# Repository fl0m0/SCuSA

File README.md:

# SCuSA
 **S**cope **Cu**rrent **S**ense **A**mplifier, work in progress

# Design goals

The main reason I designed this current sense amplifier was the need to verify power supplys on PCBs:

* Turn on behavior
* Inrush current
* Short circuit current
* Ripple current

My main requirements were:

* High side measurement > 60 V
* Common mode input range down to 0 V
* Burden voltage below 150 mV
* No galvanic isolation
* Current range up to approx ~3 A
* Accuracy better than 2%
* Bandwith > 150 kHz
* Bonus: Measurement of negative current (for battery charging applications)

I had already built a simple current sense amplifier based on the [INA169](https://www.ti.com/product/INA169) on a breadboard. It fullfilled most of my requirements except the common mode voltage range: 2.7 V made it impossible to measure 1.8 V or 1.0 V voltage supplies which are quite common these days.

I ended up with a design way to complicated and expensive :-) But I really wanted to try out a few interesting ICs:

* [LM27762](https://www.ti.com/product/LM27762): "Low-Noise Positive and Negative Output Integrated Charge Pump Plus LDO"
* [AD8210A](https://www.analog.com/en/products/ad8210.html) or [AD8418A](https://www.analog.com/en/products/ad8418a.html): Very fancy looking "High Voltage, Bidirectional Current Shunt Monitors"

# Current status

* RevA built and partially tested
* Documentation not finished
* RevB work in progress (fixed errors, improvements)

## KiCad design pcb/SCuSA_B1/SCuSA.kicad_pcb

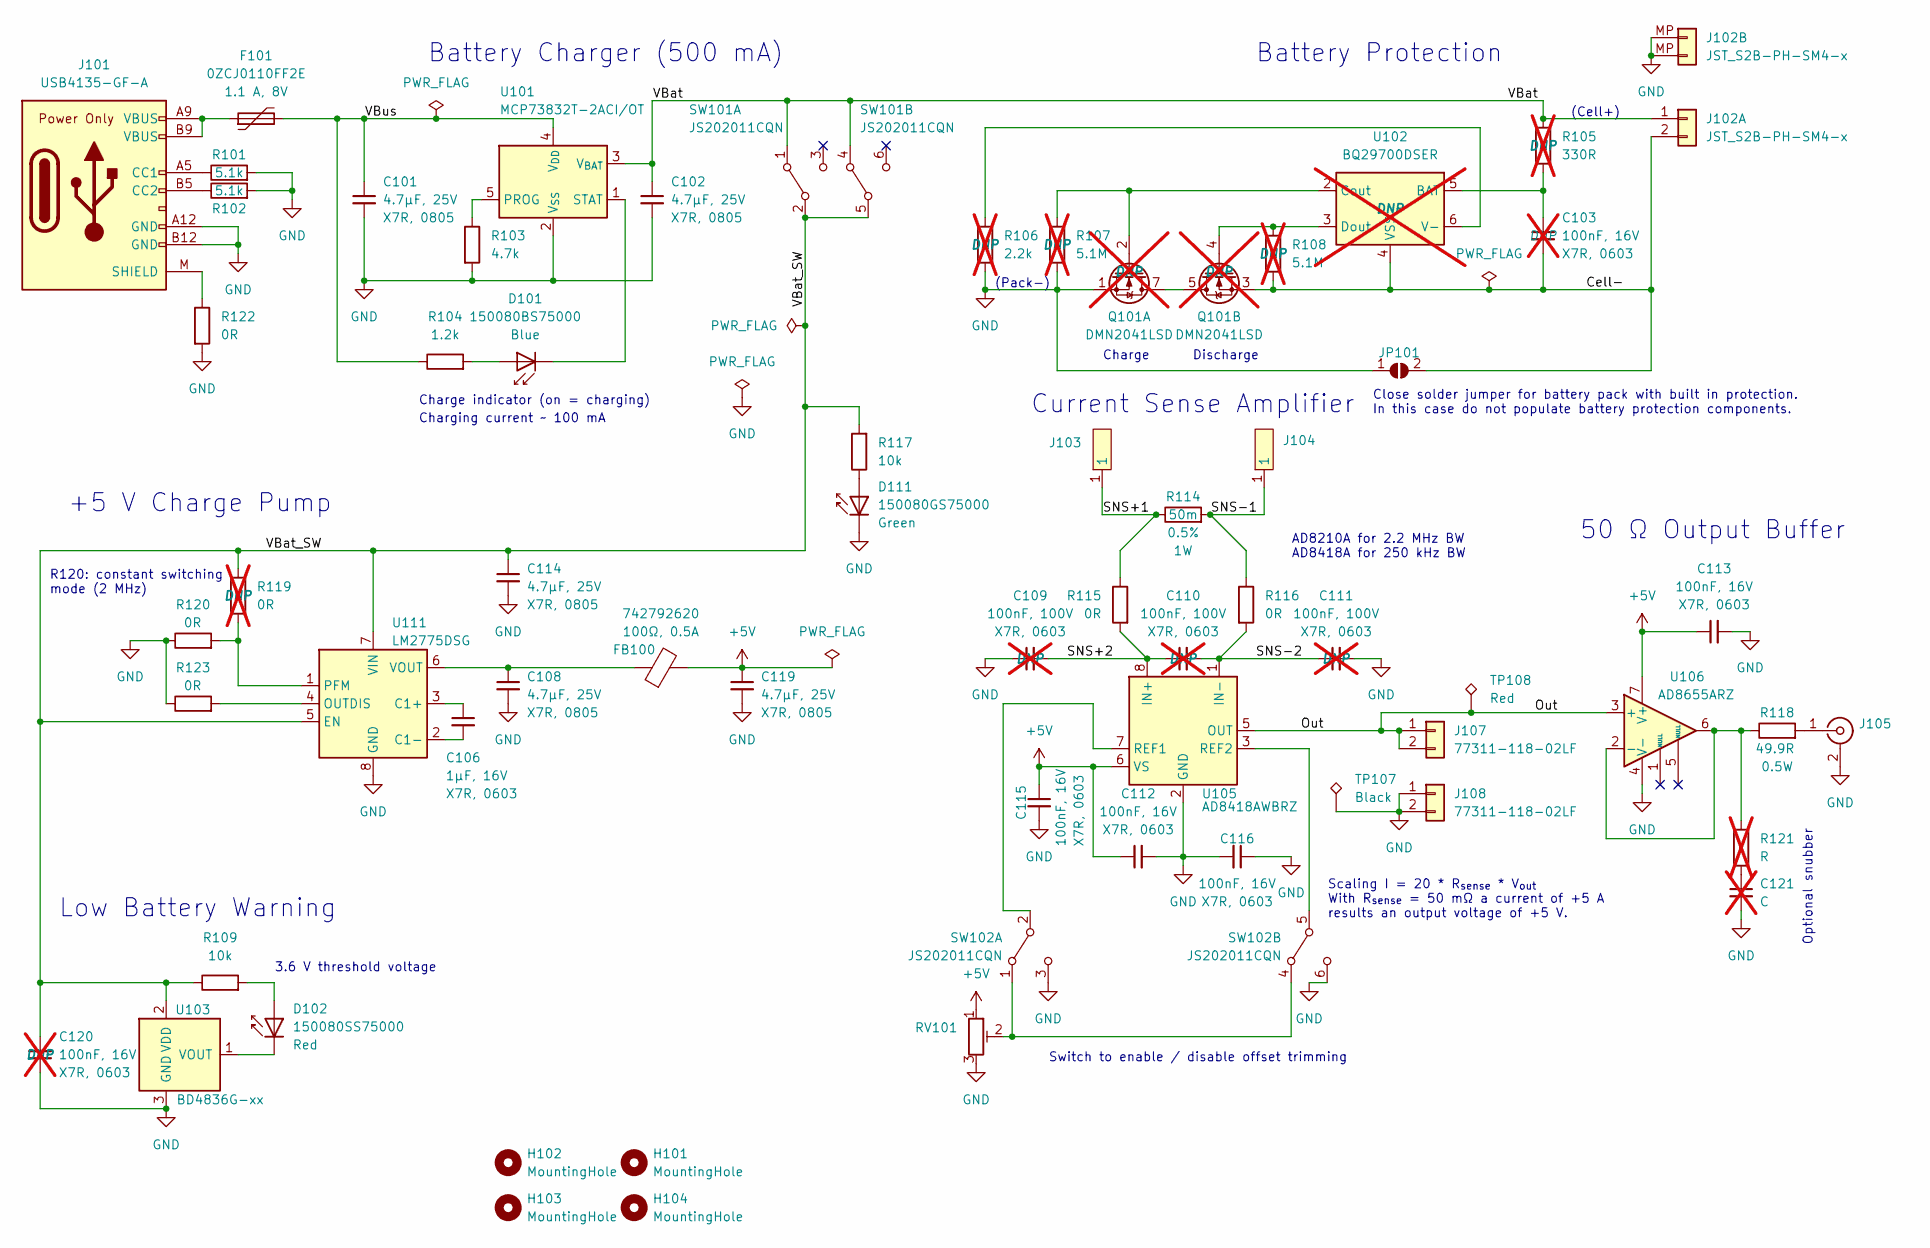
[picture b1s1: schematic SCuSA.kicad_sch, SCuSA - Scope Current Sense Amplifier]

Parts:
C101, C102, C108, C114, C119: 4.7uF,25V,X7R,0805; C_0805_2012Metric_Pad1.18x1.45mm_HandSolder
C103, C120: 100nF,16V,X7R,0603; C_0603_1608Metric_Pad1.08x0.95mm_HandSolder; not fitted
C106: 1uF,16V,X7R,0603; C_0603_1608Metric_Pad1.08x0.95mm_HandSolder
C109, C110, C111: 100nF,100V,X7R,0603; C_0603_1608Metric_Pad1.08x0.95mm_HandSolder; not fitted
C112, C113, C115, C116: 100nF,16V,X7R,0603; C_0603_1608Metric_Pad1.08x0.95mm_HandSolder
C121: C; C_0603_1608Metric_Pad1.08x0.95mm_HandSolder; not fitted
D101: 150080BS75000; LED_0805_2012Metric_Pad1.15x1.40mm_HandSolder
D102: 150080SS75000; LED_0805_2012Metric_Pad1.15x1.40mm_HandSolder
D111: 150080GS75000; LED_0805_2012Metric_Pad1.15x1.40mm_HandSolder
F101: 0ZCJ0110FF2E; Fuse_1206_3216Metric_Pad1.42x1.75mm_HandSolder; MPN 0ZCJ0110FF2E
FB100: 742792620; L_0603_1608Metric_Pad1.05x0.95mm_HandSolder; MPN 742792620
H101, H102, H103, H104: MountingHole; MountingHole_3.2mm_M3_DIN965
J101: USB4135-GF-A; USB-C_Receptacle_GTC_USB4135-GF-A; MPN USB4135-GF-A
J102: JST_S2B-PH-SM4-x; JST_PH_S2B-PH-SM4-TB_1x02-1MP_P2.00mm_Horizontal; MPN S2B-PH-SM4-TB
J103: Binding_Post_PKI_10_A_Au; Binding_Post_PKI_10_A_Au_Red; MPN 930103701
J104: Binding_Post_PKI_10_A_Au; Binding_Post_PKI_10_A_Au_Black; MPN 930103700
J105: SMA_Straight_Jack_Female; SMA_Vertical; MPN RF2-04A-T-00-50-G
J107, J108: 77311-118-02LF; PinHeader_1x02_P2.54mm_Vertical
JP101: SolderJumper_2_Open; SolderJumper-2_P1.3mm_Open_TrianglePad1.0x1.5mm
Q101: DMN2041LSD; SOIC-8_3.9x4.9mm_P1.27mm; MPN DMN2041LSD-13; not fitted
R101, R102: 5.1k,0603; R_0603_1608Metric_Pad0.98x0.95mm_HandSolder; Tolerance 1%
R103: 4.7k,0603; R_0603_1608Metric_Pad0.98x0.95mm_HandSolder; Tolerance 1%
R104: 1.2k,0603; R_0603_1608Metric_Pad0.98x0.95mm_HandSolder; Tolerance 1%
R105: 330R,0603; R_0603_1608Metric_Pad0.98x0.95mm_HandSolder; Tolerance 1%; not fitted
R106: 2.2k,0603; R_0603_1608Metric_Pad0.98x0.95mm_HandSolder; Tolerance 1%; not fitted
R107, R108: 5.1M,0603; R_0603_1608Metric_Pad0.98x0.95mm_HandSolder; Tolerance 1%; not fitted
R109, R117: 10k,0603; R_0603_1608Metric_Pad0.98x0.95mm_HandSolder; Tolerance 1%
R114: 50m; R_1206_3216Metric_Pad1.30x1.75mm_HandSolder; Tolerance 0.5%
R115, R116, R120, R122, R123: 0R,0603; R_0603_1608Metric_Pad0.98x0.95mm_HandSolder; Tolerance 1%
R118: 49.9R,1206; R_1206_3216Metric_Pad1.30x1.75mm_HandSolder; Tolerance 1%
R119: 0R,0603; R_0603_1608Metric_Pad0.98x0.95mm_HandSolder; Tolerance 1%; not fitted
R121: R; R_0603_1608Metric_Pad0.98x0.95mm_HandSolder; not fitted
RV101: 10k_Potentiometer_Trim_TSR-3296W; Potentiometer_Suntan_3296W_Vertical_90deg; MPN TSR-3296W
SW101, SW102: JS202011CQN; SW_CuK_JS202011CQN_DPDT_Straight; MPN JS202011CQN
TP107: TestPoint_5011_Black; TestPoint_Loop_D2.60mm_Drill1.6mm_Beaded; MPN 5011
TP108: TestPoint_5010_Red; TestPoint_Loop_D2.60mm_Drill1.6mm_Beaded; MPN 5010
U101: MCP73832T-2ACI/OT; SOT-23-5
U102: BQ29700DSER; WSON-6_1.5x1.5mm_P0.5mm; not fitted
U103: BD4836G-xx; SOT-23-5; MPN BD4836G-xx
U105: AD8418AWBRZ; SOIC-8_3.9x4.9mm_P1.27mm; MPN AD8418AWBRZ
U106: AD8655ARZ; SOIC-8_3.9x4.9mm_P1.27mm
U111: LM2775DSG; WSON-8-1EP_2x2mm_P0.5mm_EP0.9x1.6mm_ThermalVias

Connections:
+5V: C112.1, C113.1, C115.1, C119.1, FB100.2, RV101.1, U105.6 (VS), U106.7 (V+)
/Cell-: C103.2, J102.2, JP101.2 (B), Q101.3 (S2), R108.2, U102.4 (VSS)
/Out: J107.1, J107.2, TP108.1, U105.5 (OUT), U106.3 (+)
/SNS+1: J103.1, R114.1, R115.1
/SNS+2: C109.2, C110.1, R115.2, U105.8 (IN+)
/SNS-1: J104.1, R114.2, R116.1
/SNS-2: C110.2, C111.1, R116.2, U105.1 (IN-)
/VBat: C102.1, J102.1, R105.1, SW101.1 (A), SW101.4 (A), U101.3 (V_{BAT})
/VBat_SW: C114.1, C120.2, R109.1, R117.2, R119.1, SW101.2 (B), SW101.5 (B), U103.2 (VDD), U111.5 (EN), U111.7 (VIN)
/VBus: C101.1, F101.2, R104.1, U101.4 (V_{DD})
GND: C101.2, C102.2, C108.2, C109.1, C111.2, C112.2, C113.2, C114.2, C115.2, C116.1, C116.2, C119.2, C120.1, C121.2, D111.1 (K), J101.A12 (GND), J101.B12 (GND), J102.MP, J105.2 (Ext), J108.1, J108.2, JP101.1 (A), Q101.1 (S1), R101.2, R102.2, R103.2, R106.2, R107.2, R120.1, R122.2, R123.1, RV101.3, SW102.3 (C), SW102.6 (C), TP107.1, U101.2 (V_{SS}), U103.3 (GND), U105.2 (GND), U106.4 (V-), U111.8 (GND), U111.9 (GND)
unnamed: C121.1, R121.2
unnamed: D101.2 (A), R104.2
unnamed: D101.1 (K), U101.1 (STAT)
unnamed: D102.2 (A), R109.2
unnamed: D102.1 (K), U103.1 (VOUT)
unnamed: D111.2 (A), R117.1
unnamed: F101.1, J101.A9 (VBUS), J101.B9 (VBUS)
unnamed: J101.A5 (CC1), R101.1
unnamed: J101.B5 (CC2), R102.1
unnamed: J101.M (SHIELD), R122.1
unnamed: J105.1 (In), R118.2
unnamed: Q101.5 (D2), Q101.6 (D2), Q101.7 (D1), Q101.8 (D1)
unnamed: Q101.2 (G1), R107.1, U102.2 (Cout)
unnamed: Q101.4 (G2), R108.1, U102.3 (Dout)
unnamed: RV101.2, SW102.1 (A), SW102.4 (A)
unnamed: SW102.2 (B), U105.7 (REF1)
unnamed: SW102.5 (B), U105.3 (REF2)
unnamed: R103.1, U101.5 (PROG)
unnamed: C103.1, R105.2, U102.5 (BAT)
unnamed: R106.1, U102.6 (V-)
unnamed: R118.1, R121.1, U106.2 (-), U106.6
unnamed: C106.1, U111.3 (C1+)
unnamed: C106.2, U111.2 (C1-)
unnamed: R123.2, U111.4 (OUTDIS)
unnamed: R119.2, R120.2, U111.1 (PFM)
unnamed: C108.1, FB100.1, U111.6 (VOUT)

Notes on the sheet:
+5 V Charge Pump
Charge
Battery Protection
Charging current ~ 100 mA
Optional snubber
Switch to enable / disable offset trimming
3.6 V threshold voltage
Current Sense Amplifier
(Pack-)
Discharge
(Cell+)
Close solder jumper for battery pack with built in protection. In this case do not populate battery protection components.
Battery Charger (500 mA)
Low Battery Warning
Scaling I = 20 * R_{sense} * V_{out} With R_{sense} = 50 mΩ a current of +5 A results an output voltage of +5 V.
Charge indicator (on = charging)
R120: constant switching mode (2 MHz)
AD8210A for 2.2 MHz BW AD8418A for 250 kHz BW
50 Ω Output Buffer

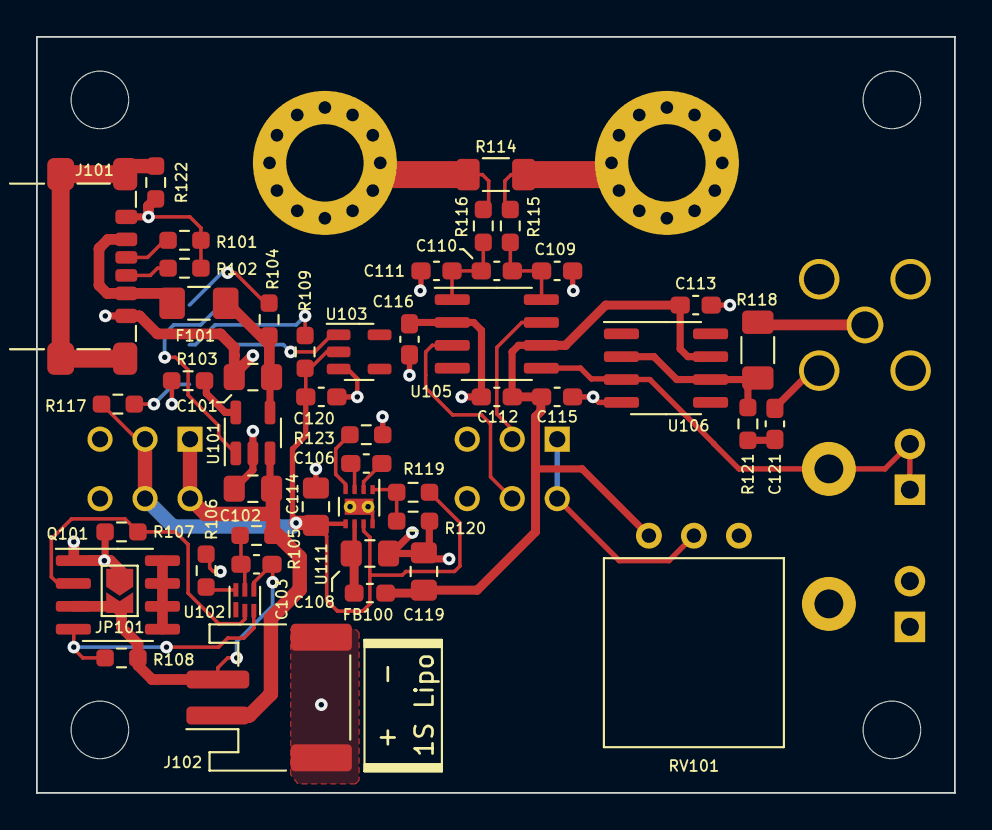
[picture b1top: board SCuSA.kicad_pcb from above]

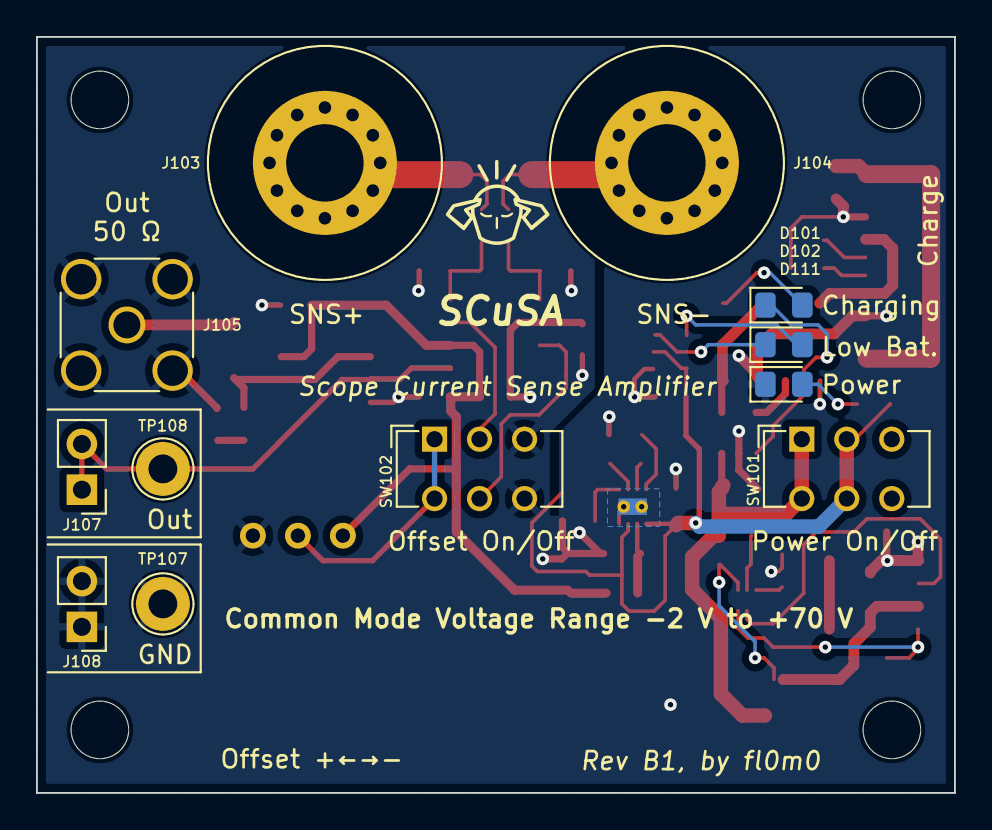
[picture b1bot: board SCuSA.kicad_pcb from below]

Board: 2 copper layers, 51.0 x 42.0 mm, 64 parts (12 on the bottom side), 37 nets.

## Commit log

2023-05-30 Create KiCad project
2023-05-31 Add alternative part simulation
2023-05-31 Switch to LM27762
2023-05-31 Add power supply
2023-06-01 Add battery circuit
2023-06-01 Work on battery charger
2023-06-02 Change battery charger
2023-06-02 Add trimpot, bindingpost
2023-06-03 Completion of schematic (for now)
2023-06-04 Add connectors, supply voltage filter
2023-06-04 Preliminary BOM
2023-06-06 Work on PCB layout
2023-06-08 Edit PCB layout
2023-06-18 Change binding posts and GND planes
2023-07-01 Fix errors, edit PCB layout
2023-07-02 Minor SCH and PCB modifications
2023-07-02 RevA1
2023-07-02 Add ibom, Aisler project ID
2023-07-15 Add notes from HW bring up
2023-07-15 Add new revision B1
2023-07-16 Increase charge current, change LED resistors
2023-07-22 Finalize case, change binding post pad
2023-07-23 Increase case dimensions
2023-07-23 Add lid to case
2023-07-26 Add measurements
2023-07-27 Modify lid case
    USB cutout, countersunk
2023-08-04 Edit documentation
2023-08-04 Remove white spaces from image file names
2023-08-06 Fix TLV803EA30DBZR (non-R pinout)
2023-08-16 Update documentation
2023-08-19 Change charge pump
2023-08-19 Change voltage supervisor
2023-08-21 PCB RevB1
2023-08-23 BOM modifications
2023-08-24 Add case for RevB1
2023-08-31 Create documentation for RevB1
2023-09-04 Update documentation, add Cura project
